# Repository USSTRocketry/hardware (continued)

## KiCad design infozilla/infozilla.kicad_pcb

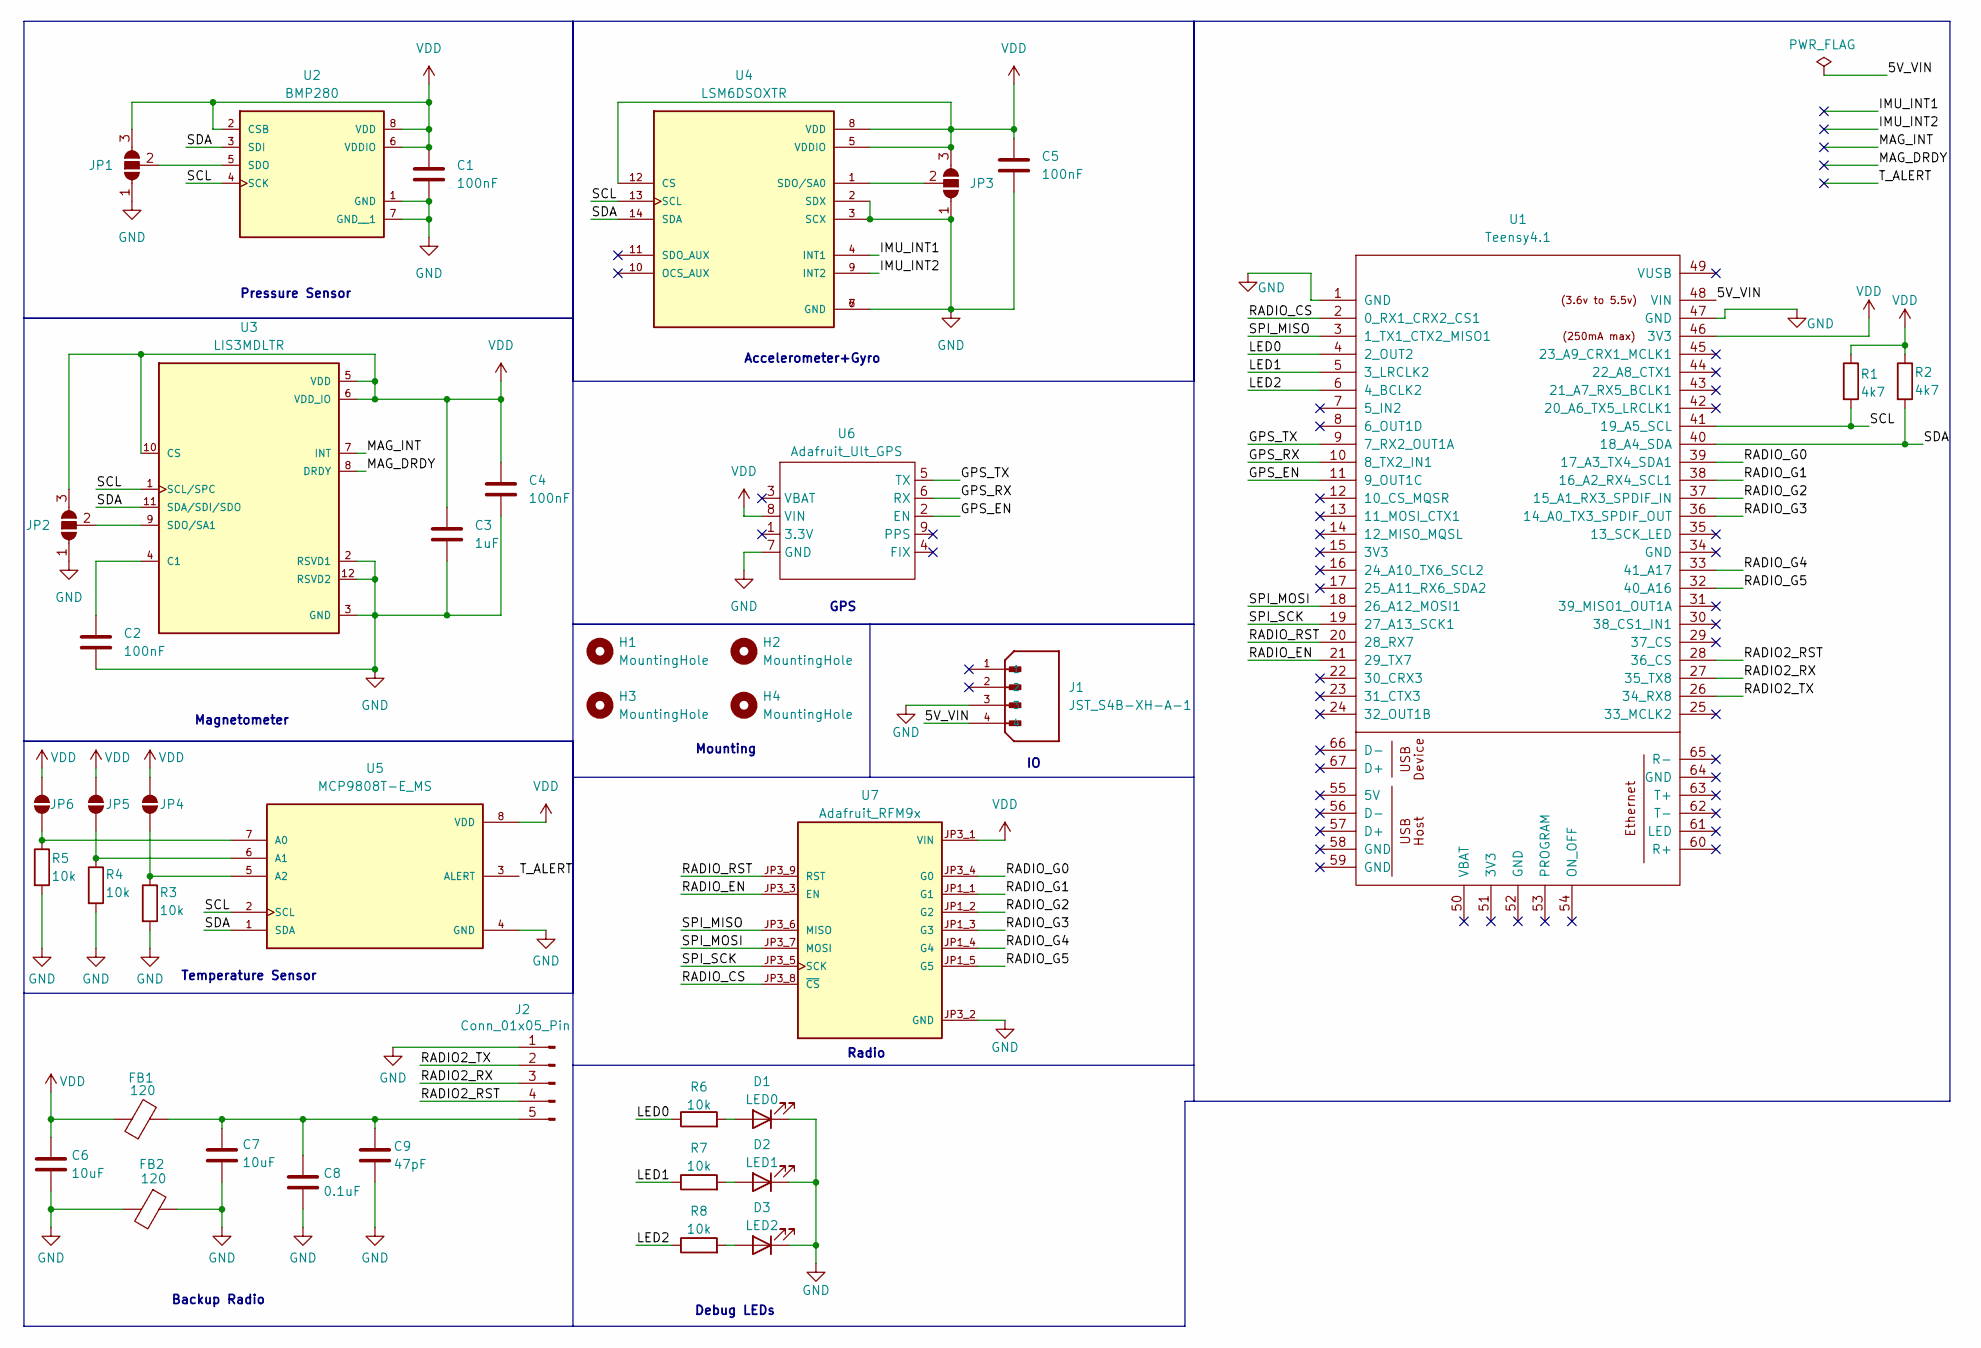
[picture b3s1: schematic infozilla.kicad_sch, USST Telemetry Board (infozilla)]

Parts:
C1, C2, C4, C5: 100nF; C_0805_2012Metric
C3: 1uF; C_0805_2012Metric
C6, C7: 10uF; C_0805_2012Metric
C8: 0.1uF; C_0805_2012Metric
C9: 47pF; C_0805_2012Metric
D1: LED0; LED_0603_1608Metric
D2: LED1; LED_0603_1608Metric
D3: LED2; LED_0603_1608Metric
FB1, FB2: 120; L_0402_1005Metric
H1, H2, H3, H4: MountingHole; MountingHole_3.2mm_M3
J1: JST_S4B-XH-A-1; PARTREV 27-1-20
J2: Conn_01x05_Pin; PinHeader_1x05_P2.54mm_Vertical
JP1, JP2, JP3: SolderJumper_3_Open; SolderJumper-3_P1.3mm_Open_Pad1.0x1.5mm_NumberLabels
JP4, JP5, JP6: SolderJumper_2_Open; SolderJumper-2_P1.3mm_Open_Pad1.0x1.5mm
R1, R2: 4k7; R_0805_2012Metric
R3, R4, R5, R6, R7, R8: 10k; R_0805_2012Metric
U1: Teensy4.1; Teensy41
U2: BMP280; PART_REV 1.19
U3: LIS3MDLTR; PARTREV 6
U4: LSM6DSOXTR; PARTREV 3.0
U5: MCP9808T-E_MS
U6: Adafruit_Ult_GPS
U7: Adafruit_RFM9x; Adafuit_RFM9x; PARTREV 2023-10-24

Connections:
/5V_VIN: J1.4, U1.48 (VIN)
/GPS_EN: U1.11 (9_OUT1C), U6.2 (EN)
/GPS_RX: U1.10 (8_TX2_IN1), U6.6 (RX)
/GPS_TX: U1.9 (7_RX2_OUT1A), U6.5 (TX)
/IMU_INT1: U4.4 (INT1)
/IMU_INT2: U4.9 (INT2)
/LED0: R6.1, U1.4 (2_OUT2)
/LED1: R7.1, U1.5 (3_LRCLK2)
/LED2: R8.1, U1.6 (4_BCLK2)
/MAG_DRDY: U3.8 (DRDY)
/MAG_INT: U3.7 (INT)
/RADIO2_RST: J2.4, U1.28 (36_CS)
/RADIO2_RX: J2.3, U1.27 (35_TX8)
/RADIO2_TX: J2.2, U1.26 (34_RX8)
/RADIO_CS: U1.2 (0_RX1_CRX2_CS1), U7.JP3_8 (~CS)
/RADIO_EN: U1.21 (29_TX7), U7.JP3_3 (EN)
/RADIO_G0: U1.39 (17_A3_TX4_SDA1), U7.JP3_4 (G0)
/RADIO_G1: U1.38 (16_A2_RX4_SCL1), U7.JP1_1 (G1)
/RADIO_G2: U1.37 (15_A1_RX3_SPDIF_IN), U7.JP1_2 (G2)
/RADIO_G3: U1.36 (14_A0_TX3_SPDIF_OUT), U7.JP1_3 (G3)
/RADIO_G4: U1.33 (41_A17), U7.JP1_4 (G4)
/RADIO_G5: U1.32 (40_A16), U7.JP1_5 (G5)
/RADIO_RST: U1.20 (28_RX7), U7.JP3_9 (RST)
/SCL: R1.2, U1.41 (19_A5_SCL), U2.4 (SCK), U3.1 (SCL/SPC), U4.13 (SCL), U5.2 (SCL)
/SDA: R2.2, U1.40 (18_A4_SDA), U2.3 (SDI), U3.11 (SDA/SDI/SDO), U4.14 (SDA), U5.1 (SDA)
/SPI_MISO: U1.3 (1_TX1_CTX2_MISO1), U7.JP3_6 (MISO)
/SPI_MOSI: U1.18 (26_A12_MOSI1), U7.JP3_7 (MOSI)
/SPI_SCK: U1.19 (27_A13_SCK1), U7.JP3_5 (SCK)
/T_ALERT: U5.3 (ALERT)
GND: C1.2, C2.2, C3.2, C4.2, C5.1, C6.2, C7.2, C8.2, C9.2, D1.1 (K), D2.1 (K), D3.1 (K), FB2.1, FB2.2, J1.3, J2.1, JP1.1 (A), JP2.1 (A), JP3.1 (A), R3.2, R4.2, R5.2, U1.1 (GND), U1.47 (GND), U2.1 (GND), U2.7 (GND__1), U3.2 (RSVD1), U3.3 (GND), U3.12 (RSVD2), U4.2 (SDX), U4.3 (SCX), U4.6 (GND), U4.7 (GND), U5.4 (GND), U6.7 (GND), U7.JP3_2 (GND)
unnamed: D1.2 (A), R6.2
unnamed: D2.2 (A), R7.2
unnamed: D3.2 (A), R8.2
unnamed: C7.1, C8.1, C9.1, FB1.2, J2.5
unnamed: JP1.2 (C), U2.5 (SDO)
unnamed: JP2.2 (C), U3.9 (SDO/SA1)
unnamed: JP3.2 (C), U4.1 (SDO/SA0)
unnamed: JP4.1 (A), R3.1, U5.5 (A2)
unnamed: JP5.1 (A), R4.1, U5.6 (A1)
unnamed: JP6.1 (A), R5.1, U5.7 (A0)
unnamed: C2.1, U3.4 (C1)
VDD: C1.1, C3.1, C4.1, C5.2, C6.1, FB1.1, JP1.3 (B), JP2.3 (B), JP3.3 (B), JP4.2 (B), JP5.2 (B), JP6.2 (B), R1.1, R2.1, U1.46 (3V3), U2.2 (CSB), U2.6 (VDDIO), U2.8 (VDD), U3.5 (VDD), U3.6 (VDD_IO), U3.10 (CS), U4.5 (VDDIO), U4.8 (VDD), U4.12 (CS), U5.8 (VDD), U6.8 (VIN), U7.JP3_1 (VIN)

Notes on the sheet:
Radio
Mounting
Magnetometer
Debug LEDs
Backup Radio
Pressure Sensor
Temperature Sensor
GPS
Accelerometer+Gyro

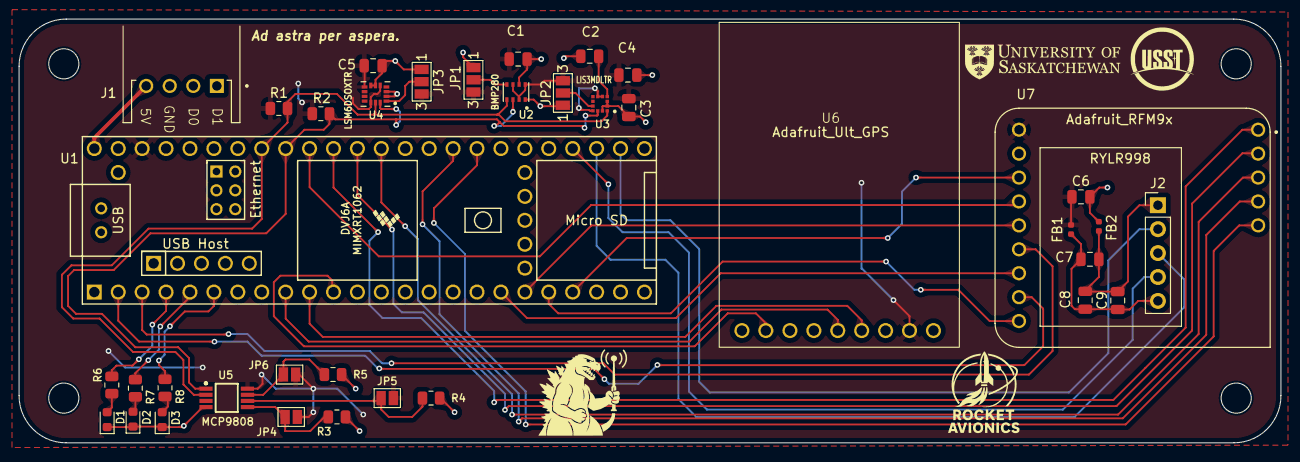
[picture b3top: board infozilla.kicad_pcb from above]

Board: 2 copper layers, 134.0 x 45.0 mm, 41 parts (0 on the bottom side), 37 nets.

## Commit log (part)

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2024-11-25 Project setup. Created projects and custom library with sensors
2024-11-25 Added teensy sym and footprint to library
2024-11-25 Moved teensy files around
2024-12-05 Telemetry board design done and flight computer board started
2024-12-05 Udated 3d models
2024-12-09 Added backup radio and debug LEDs
2025-09-03 Cutoff for LC2025
2025-09-03 Add SPI sd card
2026-05-02 Finished schematics and almost done layouts of LC26 PCBs
